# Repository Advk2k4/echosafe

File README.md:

# EchoSafe

Wearable, around-the-ear sound-alert device for people who are deaf or hard
of hearing. ESP32-S3, 4 directional MEMS mics, on-device ML sound
classification, 4 directional haptic motors.

See [`CLAUDE.md`](CLAUDE.md) for architecture, pin mapping, ML pipeline, and
current status. See [`CONSOLIDATION_NOTES.md`](CONSOLIDATION_NOTES.md) for
where this repo's contents came from.

```
firmware/   ESP32-S3 Arduino sketches (full system, single-mic reference, data collector)
ml/         Training pipeline + dataset
hardware/   5 KiCad projects: central pod + 4 earpiece modules (PCB layout not yet started)
docs/       Supplementary reference docs
```

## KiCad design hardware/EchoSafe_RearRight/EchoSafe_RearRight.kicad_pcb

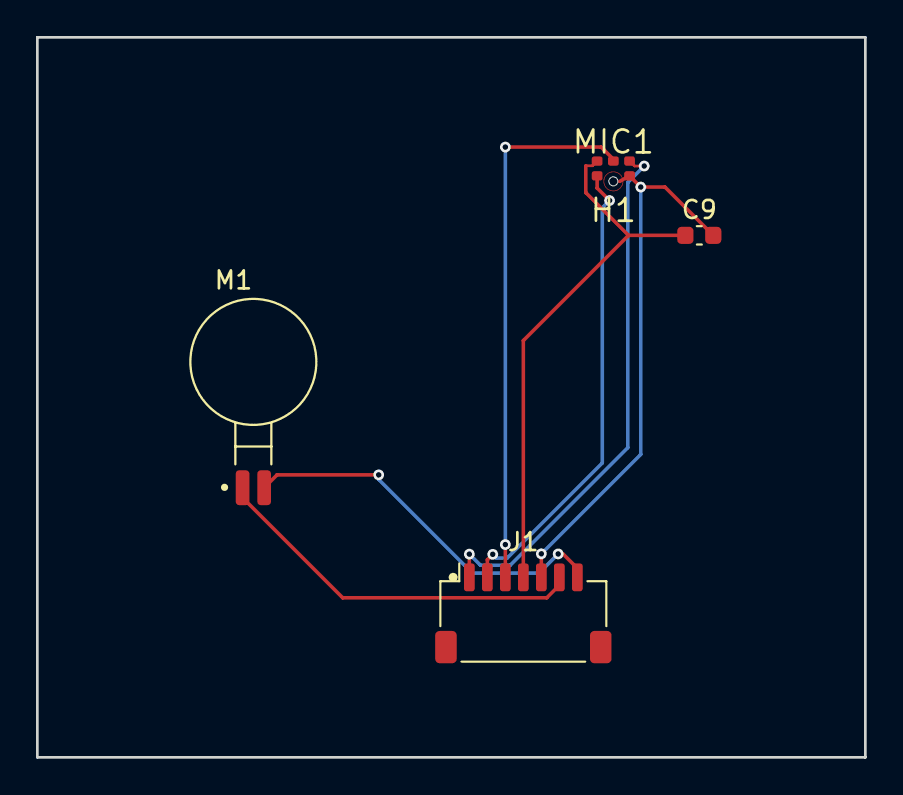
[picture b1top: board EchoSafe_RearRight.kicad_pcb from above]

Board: 2 copper layers, 46.0 x 40.0 mm, 5 parts (0 on the bottom side), 7 nets.

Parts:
C9: 1uF; C_0603_1608Metric
H1: Acoustic_Port_0.5mm
J1: JST_SH_SM07B-SRSS-TB_1x07-1MP_P1.00mm_Horizontal
M1: XDCR_C0720B001F
MIC1: ICS-43434_LGA6

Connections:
3V3_SYS: C9.1, J1.4, MIC1.5
GND: C9.2, J1.5, MIC1.2, MIC1.3
MIC_BOT_SCK: J1.2, MIC1.4
MIC_BOT_SD: J1.3, MIC1.6
MIC_BOT_WS: J1.1, MIC1.1
MOTOR_BR_OUTN: J1.7, M1.2
MOTOR_BR_OUTP: J1.6, M1.1

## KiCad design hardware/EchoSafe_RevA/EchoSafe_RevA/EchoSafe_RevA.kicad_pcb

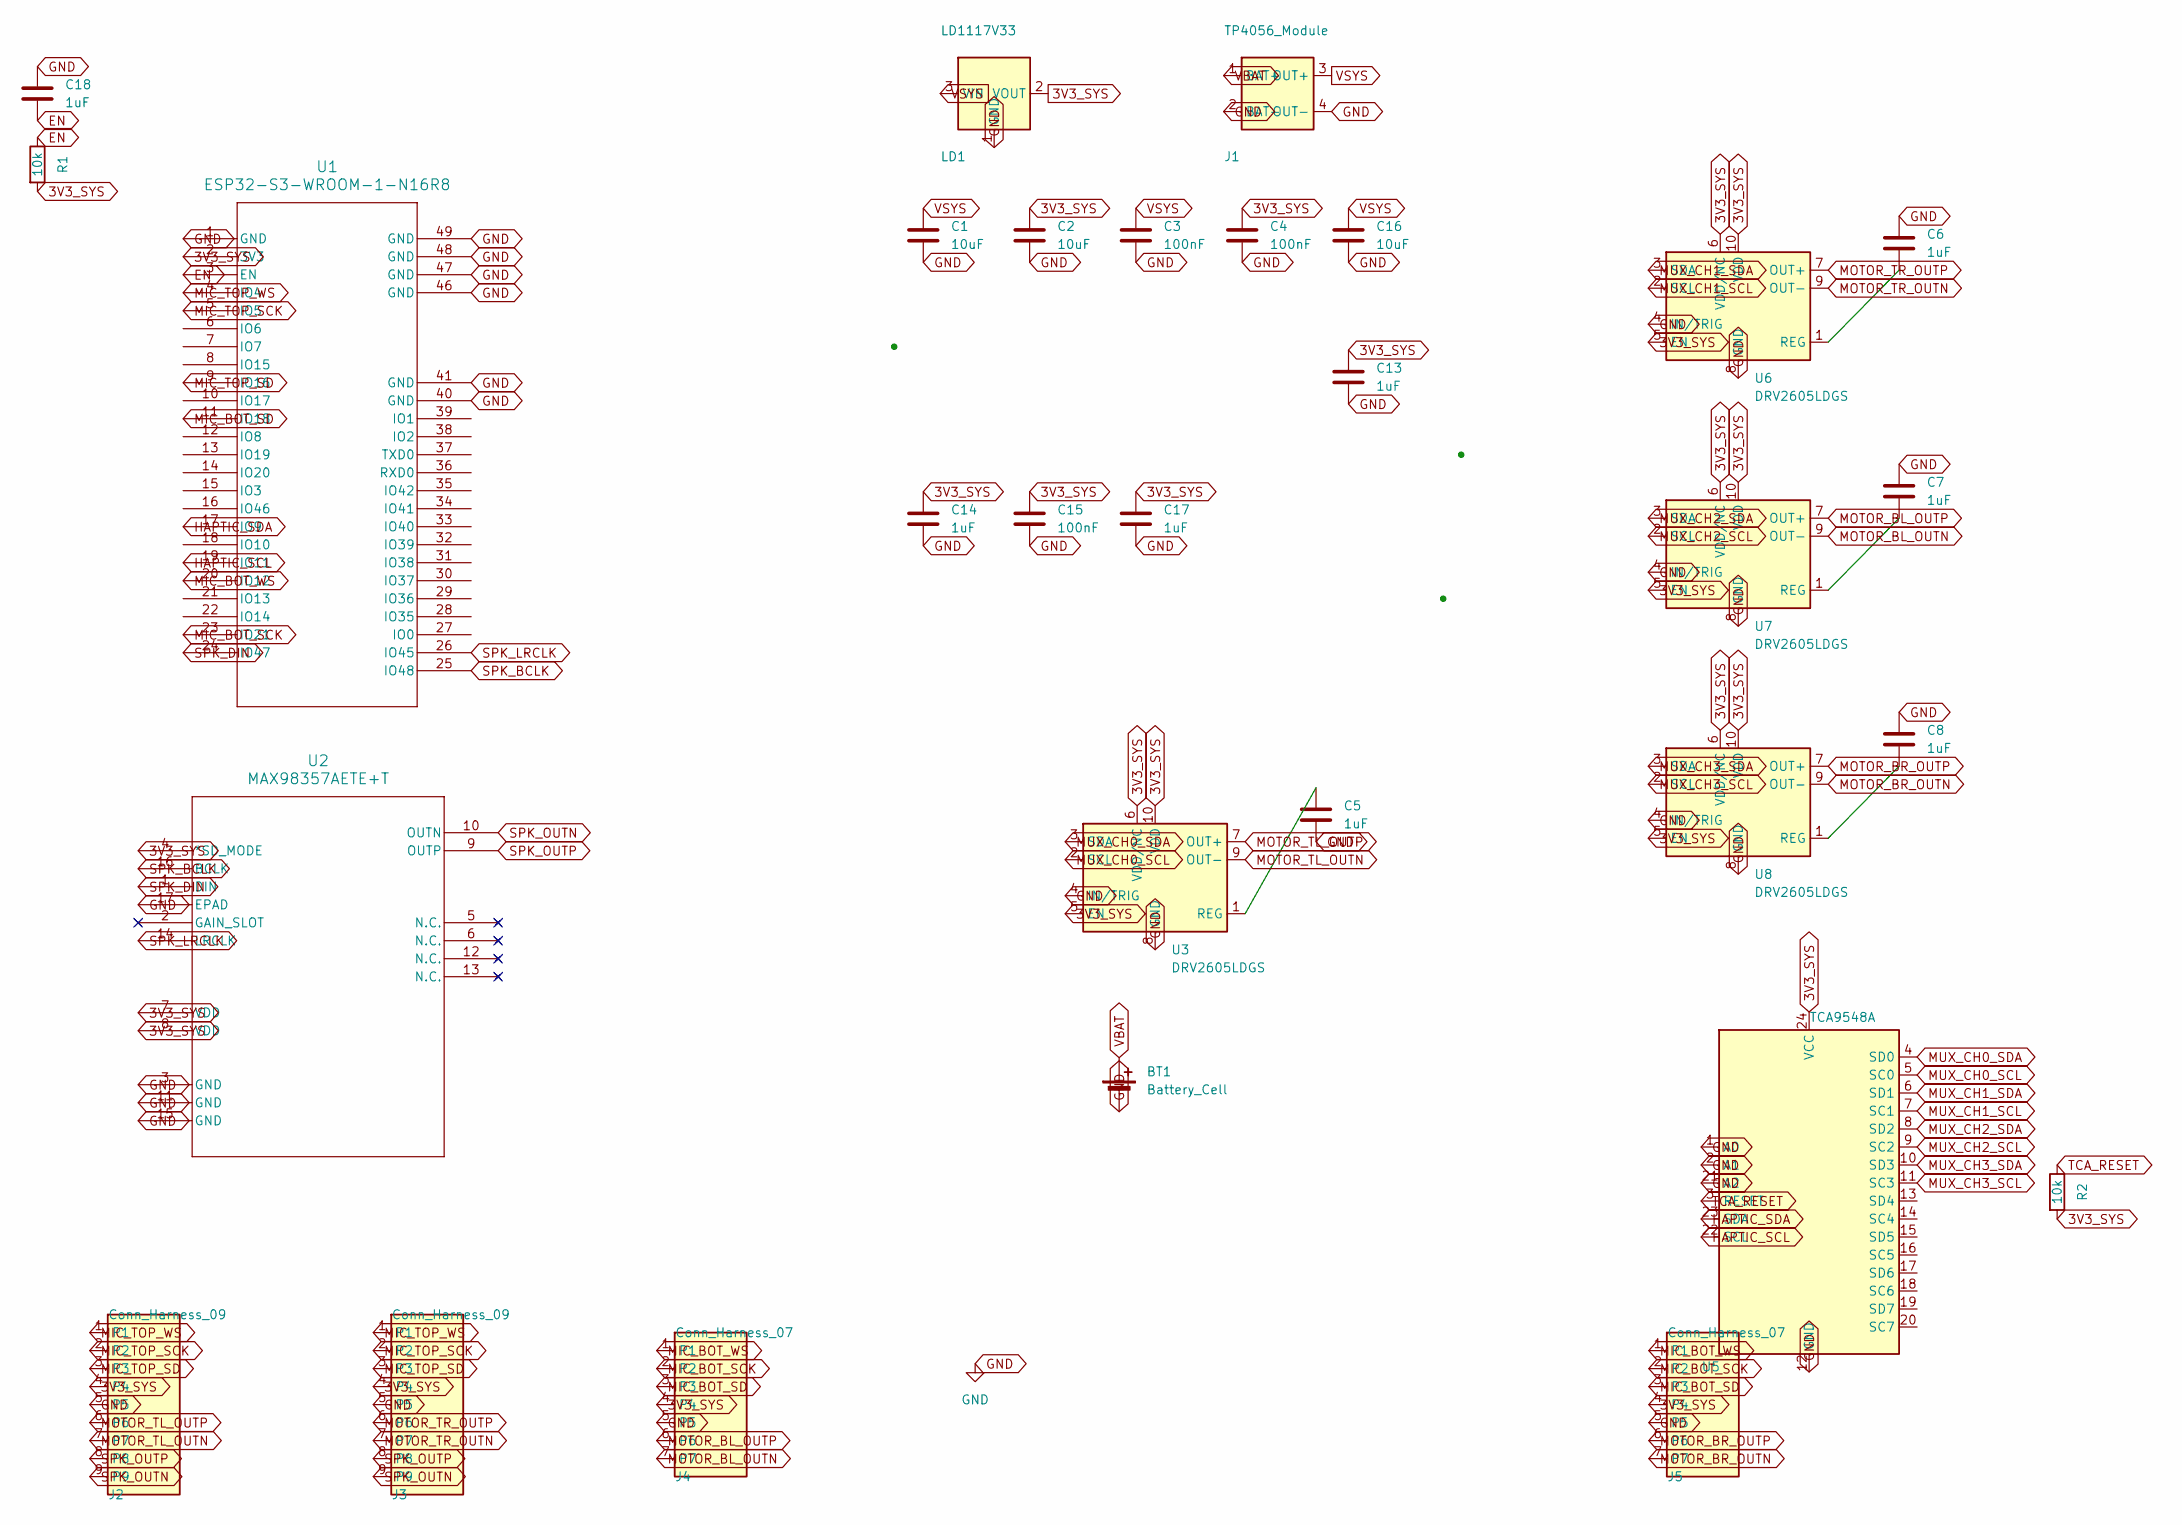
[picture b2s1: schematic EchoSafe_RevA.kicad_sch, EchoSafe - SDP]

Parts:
BT1: Battery_Cell; JST_PH_S2B-PH-K_1x02_P2.00mm_Horizontal
C1, C2, C16: 10uF; C_0603_1608Metric
C3, C4, C15: 100nF; C_0603_1608Metric
C5, C6, C7, C8, C13, C14, C17, C18: 1uF; C_0603_1608Metric
J1: TP4056_Module
J2, J3: Conn_Harness_09; JST_SH_SM09B-SRSS-TB_1x09-1MP_P1.00mm_Horizontal
J4, J5: Conn_Harness_07; JST_SH_SM07B-SRSS-TB_1x07-1MP_P1.00mm_Horizontal
LD1: LD1117V33; PinHeader_1x03_P2.54mm_Vertical
R1, R2: 10k; R_0603_1608Metric
U1: ESP32-S3-WROOM-1-N16R8; ESP32-S3-WROOM-1_EXP
U2: MAX98357AETE+T; 21-0136I_T1633-4_MXM
U3, U6, U7, U8: DRV2605LDGS; VSSOP-10_3x3mm_P0.5mm
U5: TCA9548A; TSSOP-24_4.4x7.8mm_P0.65mm

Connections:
3V3_SYS: C2.1, C4.1, C13.1, C14.1, C15.1, C17.1, J2.4, J3.4, J4.4, J5.4, LD1.2 (VOUT), R1.2, R2.2, U1.2 (3V3), U2.4 (*SD_MODE), U2.7 (VDD), U2.8 (VDD), U3.5 (EN), U3.6 (VDD/NC), U3.10 (VDD), U5.24 (VCC), U6.5 (EN), U6.6 (VDD/NC), U6.10 (VDD), U7.5 (EN), U7.6 (VDD/NC), U7.10 (VDD), U8.5 (EN), U8.6 (VDD/NC), U8.10 (VDD)
EN: C18.2, R1.1, U1.3 (EN)
GND: BT1.2 (-), C1.2, C2.2, C3.2, C4.2, C5.2, C6.1, C7.1, C8.1, C13.2, C14.2, C15.2, C16.2, C17.2, C18.1, J1.2 (BAT-), J1.4 (OUT-), J2.5, J3.5, J4.5, J5.5, LD1.1 (GND), U1.1 (GND), U1.40 (GND), U1.41 (GND), U1.46 (GND), U1.47 (GND), U1.48 (GND), U1.49 (GND), U2.3 (GND), U2.11 (GND), U2.15 (GND), U2.17 (EPAD), U3.4 (IN/TRIG), U3.8 (GND), U5.1 (A0), U5.2 (A1), U5.12 (GND), U5.21 (A2), U6.4 (IN/TRIG), U6.8 (GND), U7.4 (IN/TRIG), U7.8 (GND), U8.4 (IN/TRIG), U8.8 (GND)
HAPTIC_SCL: U1.19 (IO11), U5.22 (SCL)
HAPTIC_SDA: U1.17 (IO9), U5.23 (SDA)
MIC_BOT_SCK: J4.2, J5.2, U1.23 (IO21)
MIC_BOT_SD: J4.3, J5.3, U1.11 (IO18)
MIC_BOT_WS: J4.1, J5.1, U1.20 (IO12)
MIC_TOP_SCK: J2.2, J3.2, U1.5 (IO5)
MIC_TOP_SD: J2.3, J3.3, U1.9 (IO16)
MIC_TOP_WS: J2.1, J3.1, U1.4 (IO4)
MOTOR_BL_OUTN: J4.7, U7.9 (OUT-)
MOTOR_BL_OUTP: J4.6, U7.7 (OUT+)
MOTOR_BR_OUTN: J5.7, U8.9 (OUT-)
MOTOR_BR_OUTP: J5.6, U8.7 (OUT+)
MOTOR_TL_OUTN: J2.7, U3.9 (OUT-)
MOTOR_TL_OUTP: J2.6, U3.7 (OUT+)
MOTOR_TR_OUTN: J3.7, U6.9 (OUT-)
MOTOR_TR_OUTP: J3.6, U6.7 (OUT+)
MUX_CH0_SCL: U3.2 (SCL), U5.5 (SC0)
MUX_CH0_SDA: U3.3 (SDA), U5.4 (SD0)
MUX_CH1_SCL: U5.7 (SC1), U6.2 (SCL)
MUX_CH1_SDA: U5.6 (SD1), U6.3 (SDA)
MUX_CH2_SCL: U5.9 (SC2), U7.2 (SCL)
MUX_CH2_SDA: U5.8 (SD2), U7.3 (SDA)
MUX_CH3_SCL: U5.11 (SC3), U8.2 (SCL)
MUX_CH3_SDA: U5.10 (SD3), U8.3 (SDA)
NET_U3_REG: C5.1, U3.1 (REG)
NET_U6_REG: C6.2, U6.1 (REG)
NET_U7_REG: C7.2, U7.1 (REG)
NET_U8_REG: C8.2, U8.1 (REG)
SPK_BCLK: U1.25 (IO48), U2.16 (BCLK)
SPK_DIN: U1.24 (IO47), U2.1 (DIN)
SPK_LRCLK: U1.26 (IO45), U2.14 (LRCLK)
SPK_OUTN: J2.9, J3.9, U2.10 (OUTN)
SPK_OUTP: J2.8, J3.8, U2.9 (OUTP)
TCA_RESET: R2.1, U5.3 (RESET)
VBAT: BT1.1 (+), J1.1 (BAT+)
VSYS: C1.1, C3.1, C16.1, J1.3 (OUT+), LD1.3 (VIN)

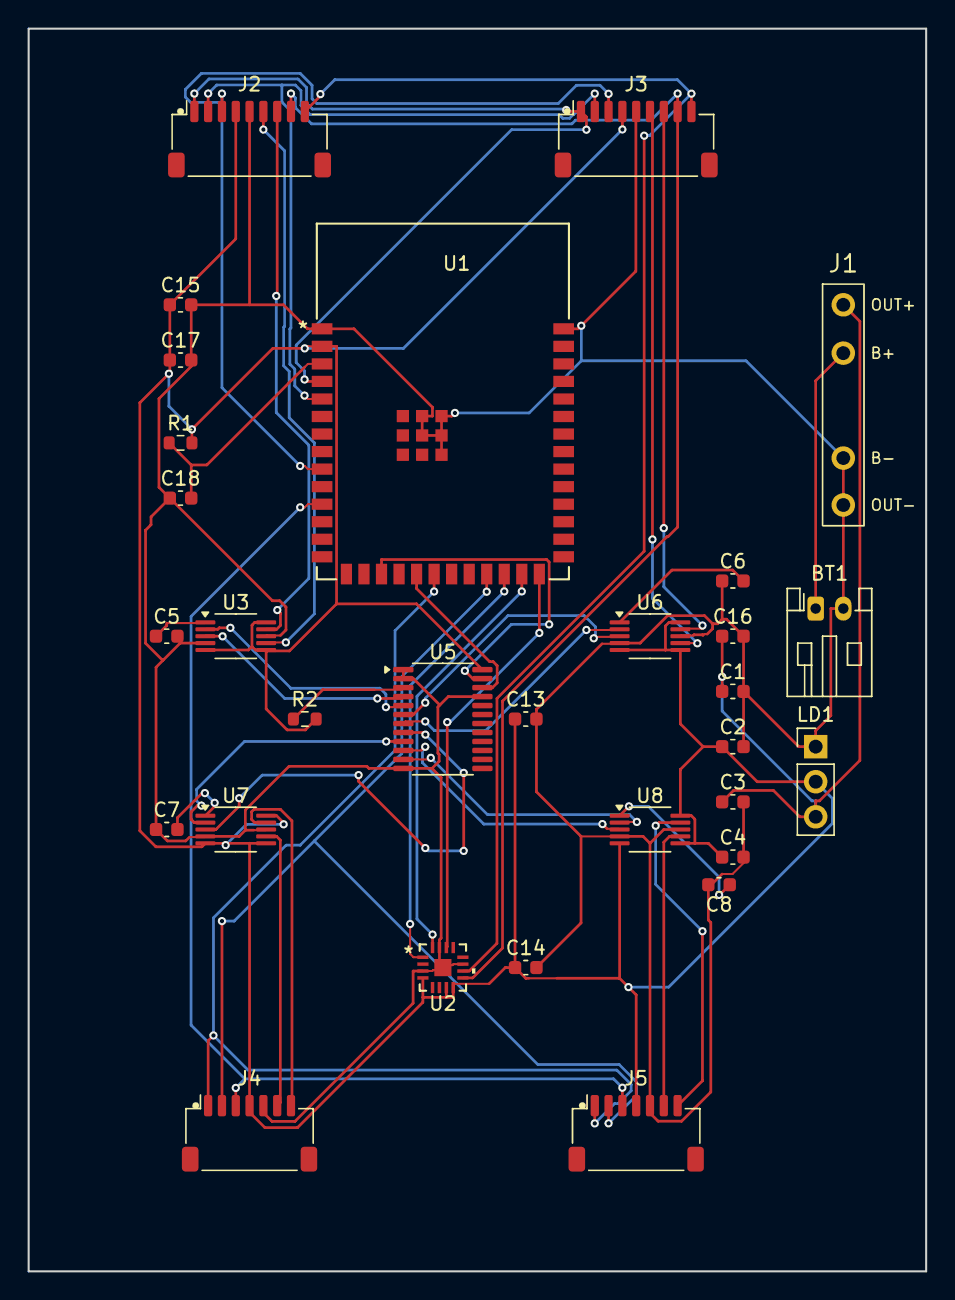
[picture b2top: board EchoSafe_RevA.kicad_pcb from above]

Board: 2 copper layers, 65.0 x 90.0 mm, 30 parts (0 on the bottom side), 39 nets.

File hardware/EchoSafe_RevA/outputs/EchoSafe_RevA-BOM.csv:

"Refs","Value","Footprint","Qty","DNP"
"BT1","Battery_Cell","Connector_JST:JST_PH_S2B-PH-K_1x02_P2.00mm_Horizontal","1",""
"C1,C2,C16","10uF","Capacitor_SMD:C_0603_1608Metric","3",""
"C3,C4,C15","100nF","Capacitor_SMD:C_0603_1608Metric","3",""
"C5,C6,C7,C8,C13,C14,C17,C18","1uF","Capacitor_SMD:C_0603_1608Metric","8",""
"J1","TP4056_Module","TP4056_Module:TP4056_Module","1",""
"J2,J3","Conn_Harness_09","Connectors_PinMarked:JST_SH_SM09B-SRSS-TB_1x09-1MP_P1.00mm_Horizontal","2",""
"J4,J5","Conn_Harness_07","Connectors_PinMarked:JST_SH_SM07B-SRSS-TB_1x07-1MP_P1.00mm_Horizontal","2",""
"LD1","LD1117V33","Connector_PinHeader_2.54mm:PinHeader_1x03_P2.54mm_Vertical","1",""
"R1,R2","10k","Resistor_SMD:R_0603_1608Metric","2",""
"U1","ESP32-S3-WROOM-1-N16R8","ESP32-S3-WROOM-1:ESP32-S3-WROOM-1_EXP","1",""
"U2","MAX98357AETE+T","MAX98357AETE-T:21-0136I_T1633-4_MXM","1",""
"U3,U6,U7,U8","DRV2605LDGS","Package_SO:VSSOP-10_3x3mm_P0.5mm","4",""
"U5","TCA9548A","Package_SO:TSSOP-24_4.4x7.8mm_P0.65mm","1",""

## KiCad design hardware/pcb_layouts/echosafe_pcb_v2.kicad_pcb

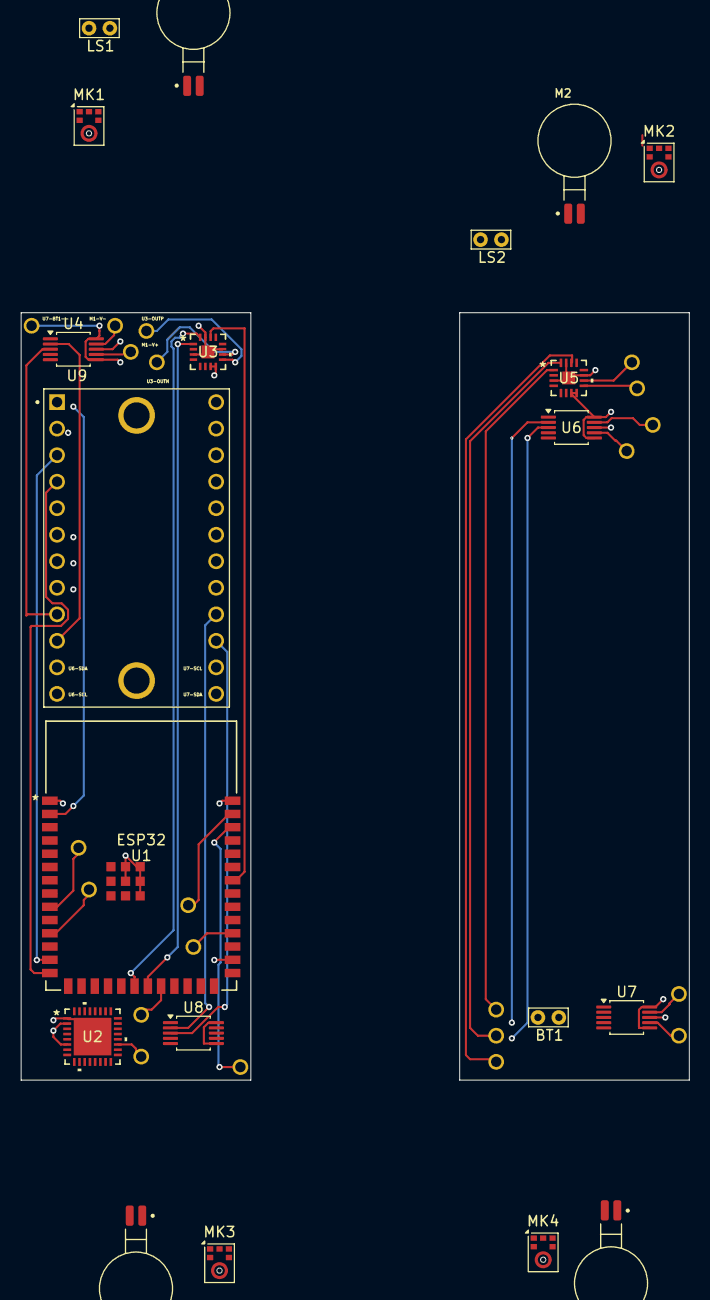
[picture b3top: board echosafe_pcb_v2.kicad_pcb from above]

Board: 4 copper layers, 20 parts (0 on the bottom side), 34 nets.

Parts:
BT1: Battery_Cell; TestPoint_Bridge_Pitch2.0mm_Drill0.7mm
LS1, LS2: Speaker; TestPoint_Bridge_Pitch2.0mm_Drill0.7mm
M1, M2, M3, M4: C0720B001F; XDCR_C0720B001F
MK1, MK2, MK3, MK4: ICS-43434; InvenSense_ICS-43434-6_3.5x2.65mm
U1: ESP32-S3-WROOM-1-N16R8; ESP32-S3-WROOM-1_EXP
U2: NPM1300-QEAA-R7; QFN32_5X5_NOR
U3: MAX98357AETE+T; 21-0136I_T1633-4_MXM-L
U4, U6, U7, U8: DRV2605LDGS; VSSOP-10_3x3mm_P0.5mm
U5: MAX98357AETE+T; 21-0136I_T1633-4_MXM
U9: 2717; MODULE_2717

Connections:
GND: MK1.2 (LR), MK1.3 (GND), MK2.3 (GND), MK3.2 (LR), MK3.3 (GND), MK4.3 (GND), U1.1 (GND), U1.28 (IO35), U1.40 (GND), U1.41 (GND), U1.46 (GND), U1.47 (GND), U1.48 (GND), U1.49 (GND), U2.2 (PVSS1), U2.6 (PVSS2), U3.3 (GND), U3.11 (GND), U3.15 (GND), U3.17 (EPAD), U4.8 (GND), U5.3 (GND), U5.11 (GND), U5.15 (GND), U5.17 (EPAD), U6.8 (GND), U7.8 (GND), U8.8 (GND), U9.2 (GND), U9.6 (A0), U9.7 (A1), U9.8 (A2)
unnamed: BT1.1 (+), U2.19 (VBAT)
unnamed: BT1.2 (-), MK1.5 (VDD), MK2.2 (LR), MK2.5 (VDD), MK3.5 (VDD), MK4.2 (LR), MK4.5 (VDD), U1.2 (3V3), U2.1 (VOUT1), U2.33 (AVSS), U3.7 (VDD), U3.8 (VDD), U4.6 (VDD/NC), U4.10 (VDD), U5.7 (VDD), U5.8 (VDD), U6.6 (VDD/NC), U6.10 (VDD), U7.6 (VDD/NC), U7.10 (VDD), U8.6 (VDD/NC), U8.10 (VDD), U9.1 (VIN)
unnamed: M1.1 (V+), U4.7 (OUT+)
unnamed: M1.2 (V-), U4.9 (OUT-)
unnamed: M2.1 (V+), U6.7 (OUT+)
unnamed: M2.2 (V-), U6.9 (OUT-)
unnamed: M3.1 (V+), U7.7 (OUT+)
unnamed: M3.2 (V-), U7.9 (OUT-)
unnamed: M4.1 (V+), U8.7 (OUT+)
unnamed: M4.2 (V-), U8.9 (OUT-)
unnamed: MK1.4 (SCK), MK2.4 (SCK), U1.39 (IO1)
unnamed: MK1.6 (SD), MK2.6 (SD), U1.9 (IO16)
unnamed: MK1.1 (WS), MK2.1 (WS), U1.38 (IO2)
unnamed: MK3.4 (SCK), MK4.4 (SCK), U1.22 (IO14)
unnamed: MK3.6 (SD), MK4.6 (SD), U1.11 (IO18)
unnamed: MK3.1 (WS), MK4.1 (WS), U1.30 (IO37)
unnamed: U1.20 (IO12), U3.16 (BCLK), U5.16 (BCLK)
unnamed: U1.21 (IO13), U3.1 (DIN), U5.1 (DIN)
unnamed: U1.13 (IO19), U9.3 (SDA)
unnamed: U1.14 (IO20), U9.4 (SCL)
unnamed: U1.34 (IO41), U3.14 (LRCLK), U5.14 (LRCLK)
unnamed: LS1.1, U3.10 (OUTN)
unnamed: LS1.1, U3.9 (OUTP)
unnamed: U4.2 (SCL), U9.10 (SCL0)
unnamed: U4.3 (SDA), U9.9 (SDA0)
unnamed: LS2.1, U5.10 (OUTN)
unnamed: LS2.1, U5.9 (OUTP)
unnamed: U6.2 (SCL), U9.12 (SCL1)
unnamed: U6.3 (SDA), U9.11 (SDA1)
unnamed: U7.2 (SCL), U9.14 (SCL2)
unnamed: U7.3 (SDA), U9.13 (SDA2)
unnamed: U8.2 (SCL), U9.16 (SCL3)
unnamed: U8.3 (SDA), U9.15 (SDA3)

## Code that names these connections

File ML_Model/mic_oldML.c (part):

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#define TDOA_MIN_RMS      0.0005f

// ── PINS (UNCHANGED) ──────────────────────────────────────────────────────────
#define MIC_TOP_WS        4
#define MIC_TOP_BCLK      5
#define MIC_TOP_DOUT      16
#define MIC_TOP_PORT      I2S_NUM_0

#define MIC_BOT_WS        12
#define MIC_BOT_BCLK      21
#define MIC_BOT_DOUT      18
#define MIC_BOT_PORT      I2S_NUM_1

#define SPK_DIN           47
#define SPK_BCLK          48
#define SPK_LRC           45
#define SPK_PORT          I2S_NUM_1

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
